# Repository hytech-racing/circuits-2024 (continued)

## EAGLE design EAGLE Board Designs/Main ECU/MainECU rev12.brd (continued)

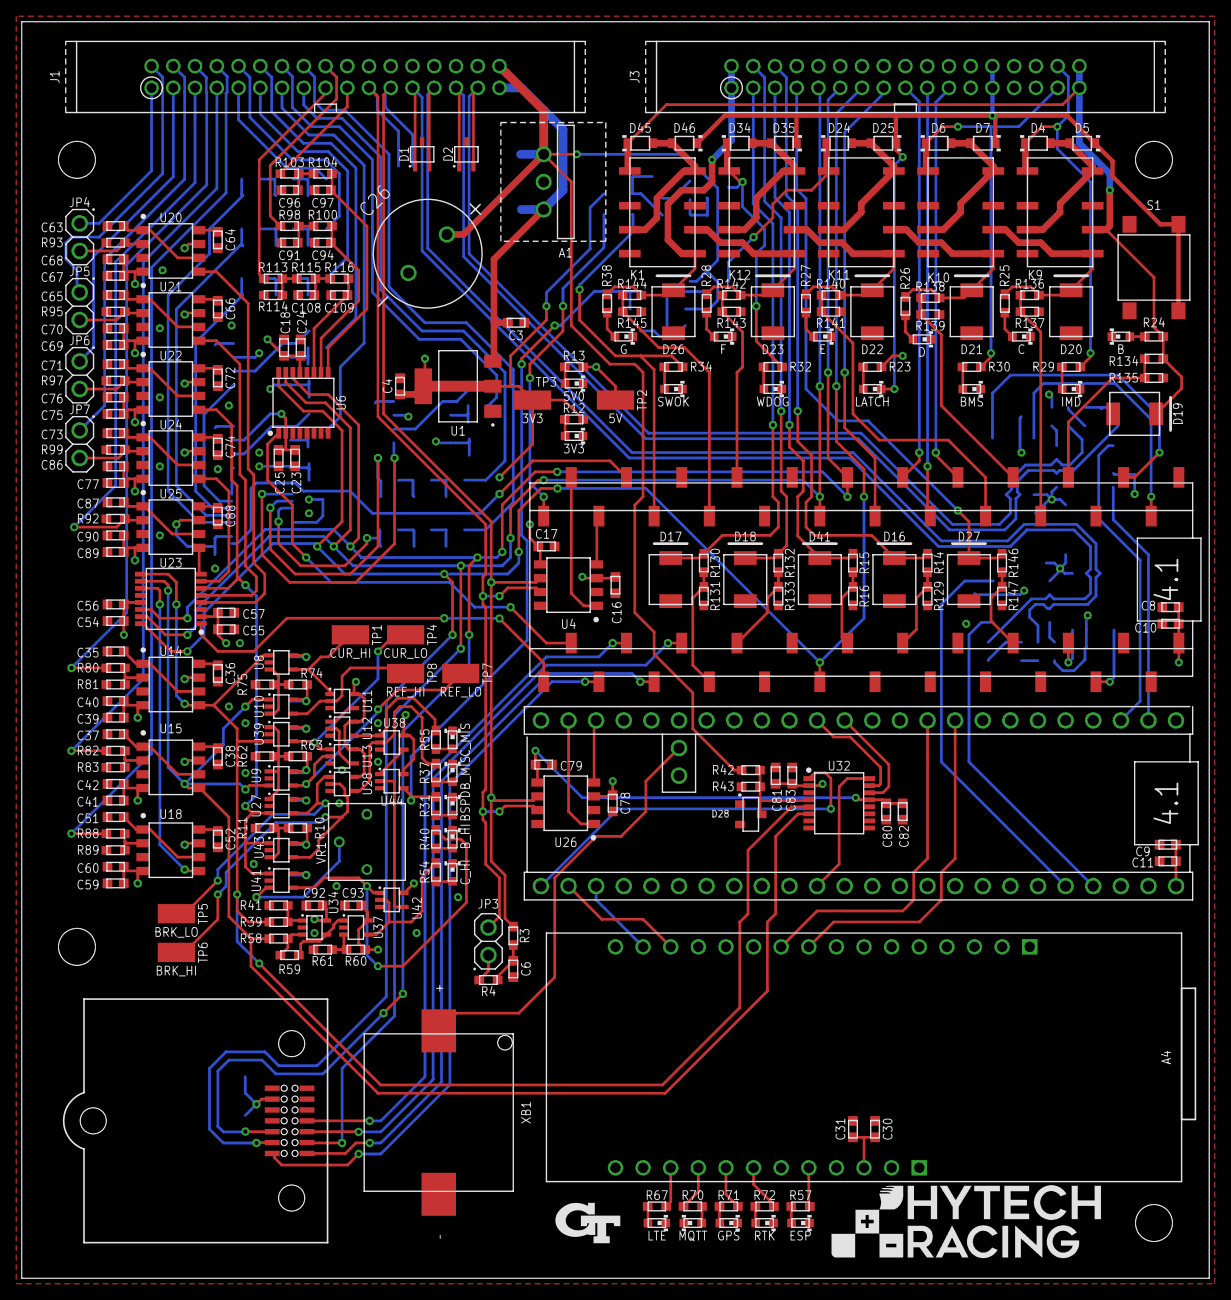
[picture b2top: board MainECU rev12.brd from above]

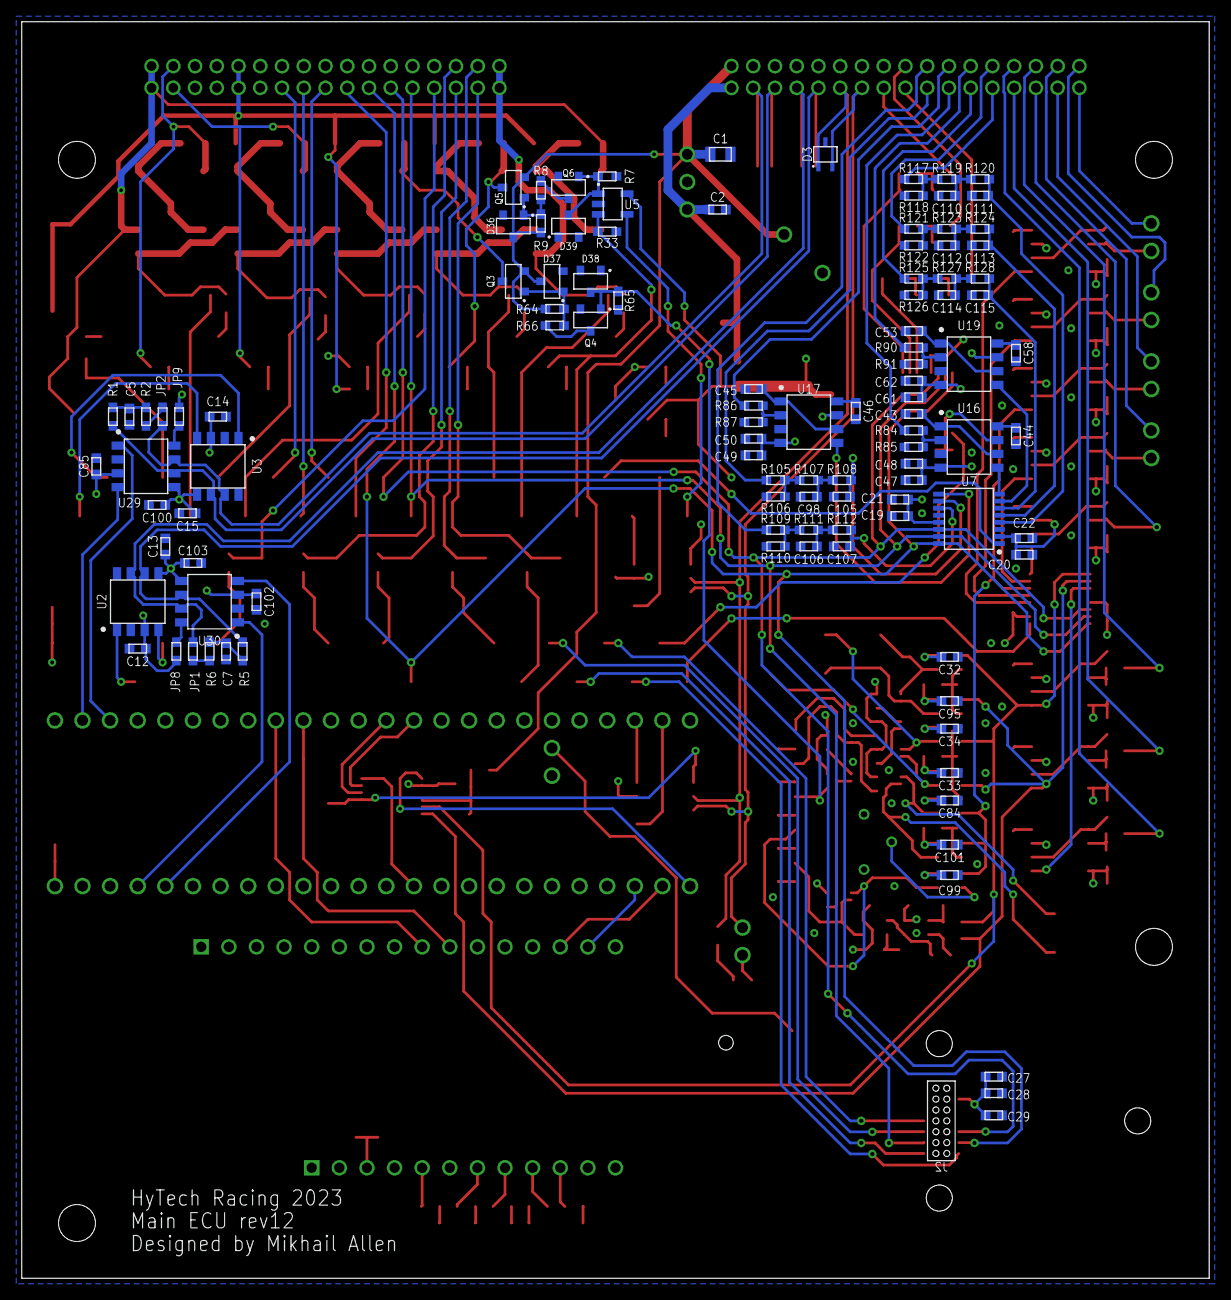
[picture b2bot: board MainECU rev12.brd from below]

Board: 4 copper layers, 109.2 x 115.6 mm, 364 parts (107 on the bottom side), 229 nets.

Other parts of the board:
U$3: LOGO_HYTECH_MEDIUM
U$5: LOGO_GT_SMALL
U$9, U$10, U$11, U$12: MOUNTING_M3

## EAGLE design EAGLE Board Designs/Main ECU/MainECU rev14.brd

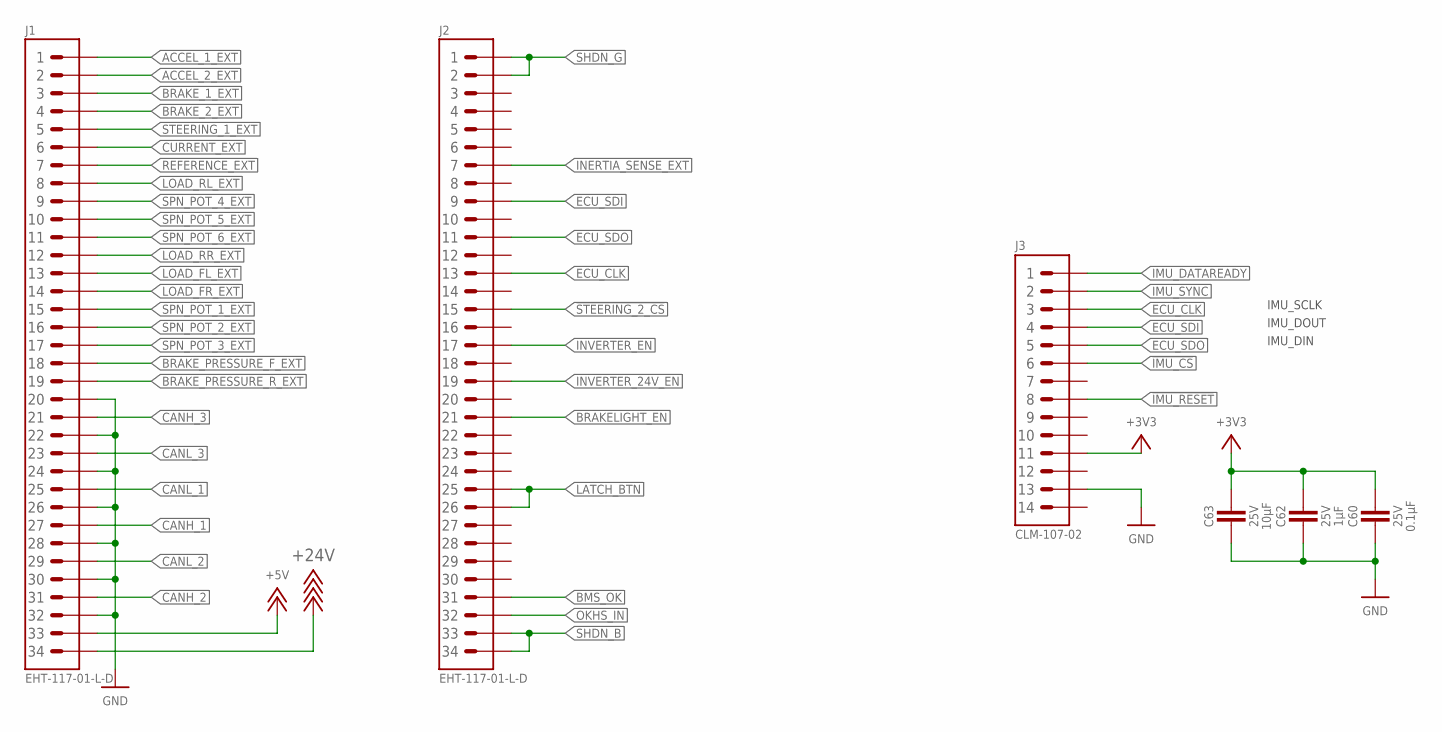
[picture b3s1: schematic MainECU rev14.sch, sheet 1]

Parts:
C60: CAPACITOR_0603_25V_0.1UF; 0603-CAP
C62: CAPACITOR_0603_25V_1UF; 0603-CAP
C63: CAPACITOR_0603_25V_10UF; 0603-CAP
J1, J2: CONNECTOR-34__; EHT-117-01
J3: ADIS16460

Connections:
!IMU_CS: J3.6; also elsewhere on the board
!IMU_RESET: J3.8; also elsewhere on the board
!STEERING_2_CS: J2.15; also elsewhere on the board
+3V3: C60.1, C62.1, C63.1, J3.11; also elsewhere on the board
+5V: J1.33; also elsewhere on the board
+24V: J1.34; also elsewhere on the board
ACCEL_1_EXT: J1.1; also elsewhere on the board
ACCEL_2_EXT: J1.2; also elsewhere on the board
BMS_OK: J2.31; also elsewhere on the board
BRAKELIGHT_EN: J2.21; also elsewhere on the board
BRAKE_1_EXT: J1.3; also elsewhere on the board
BRAKE_2_EXT: J1.4; also elsewhere on the board
BRAKE_PRESSURE_F_EXT: J1.18
BRAKE_PRESSURE_R_EXT: J1.19
CANH_1: J1.27; also elsewhere on the board
CANH_2: J1.31; also elsewhere on the board
CANH_3: J1.21; also elsewhere on the board
CANL_1: J1.25; also elsewhere on the board
CANL_2: J1.29; also elsewhere on the board
CANL_3: J1.23; also elsewhere on the board
CURRENT_EXT: J1.6; also elsewhere on the board
ECU_CLK: J2.13, J3.3; also elsewhere on the board
ECU_SDI: J2.9, J3.4; also elsewhere on the board
ECU_SDO: J2.11, J3.5; also elsewhere on the board
GND: C60.2, C62.2, C63.2, J1.20, J1.22, J1.24, J1.26, J1.28, J1.30, J1.32, J3.13; also elsewhere on the board
IMU_DATAREADY: J3.1; also elsewhere on the board
IMU_SYNC: J3.2; also elsewhere on the board
INERTIA_SENSE_EXT: J2.7; also elsewhere on the board
INVERTER_24V_EN: J2.19; also elsewhere on the board
INVERTER_EN: J2.17; also elsewhere on the board
LATCH_BTN: J2.25, J2.26; also elsewhere on the board
LOAD_FL_EXT: J1.13; also elsewhere on the board
LOAD_FR_EXT: J1.14; also elsewhere on the board
LOAD_RL_EXT: J1.8; also elsewhere on the board
LOAD_RR_EXT: J1.12; also elsewhere on the board
OKHS_IN: J2.32; also elsewhere on the board
REFERENCE_EXT: J1.7; also elsewhere on the board
SHDN_B: J2.33, J2.34; also elsewhere on the board
SHDN_G: J2.1, J2.2; also elsewhere on the board
SPN_POT_1_EXT: J1.15; also elsewhere on the board
SPN_POT_2_EXT: J1.16; also elsewhere on the board
SPN_POT_3_EXT: J1.17; also elsewhere on the board
SPN_POT_4_EXT: J1.9; also elsewhere on the board
SPN_POT_5_EXT: J1.10
SPN_POT_6_EXT: J1.11
STEERING_1_EXT: J1.5; also elsewhere on the board

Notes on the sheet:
IMU_DOUT
IMU_SCLK
IMU_DIN

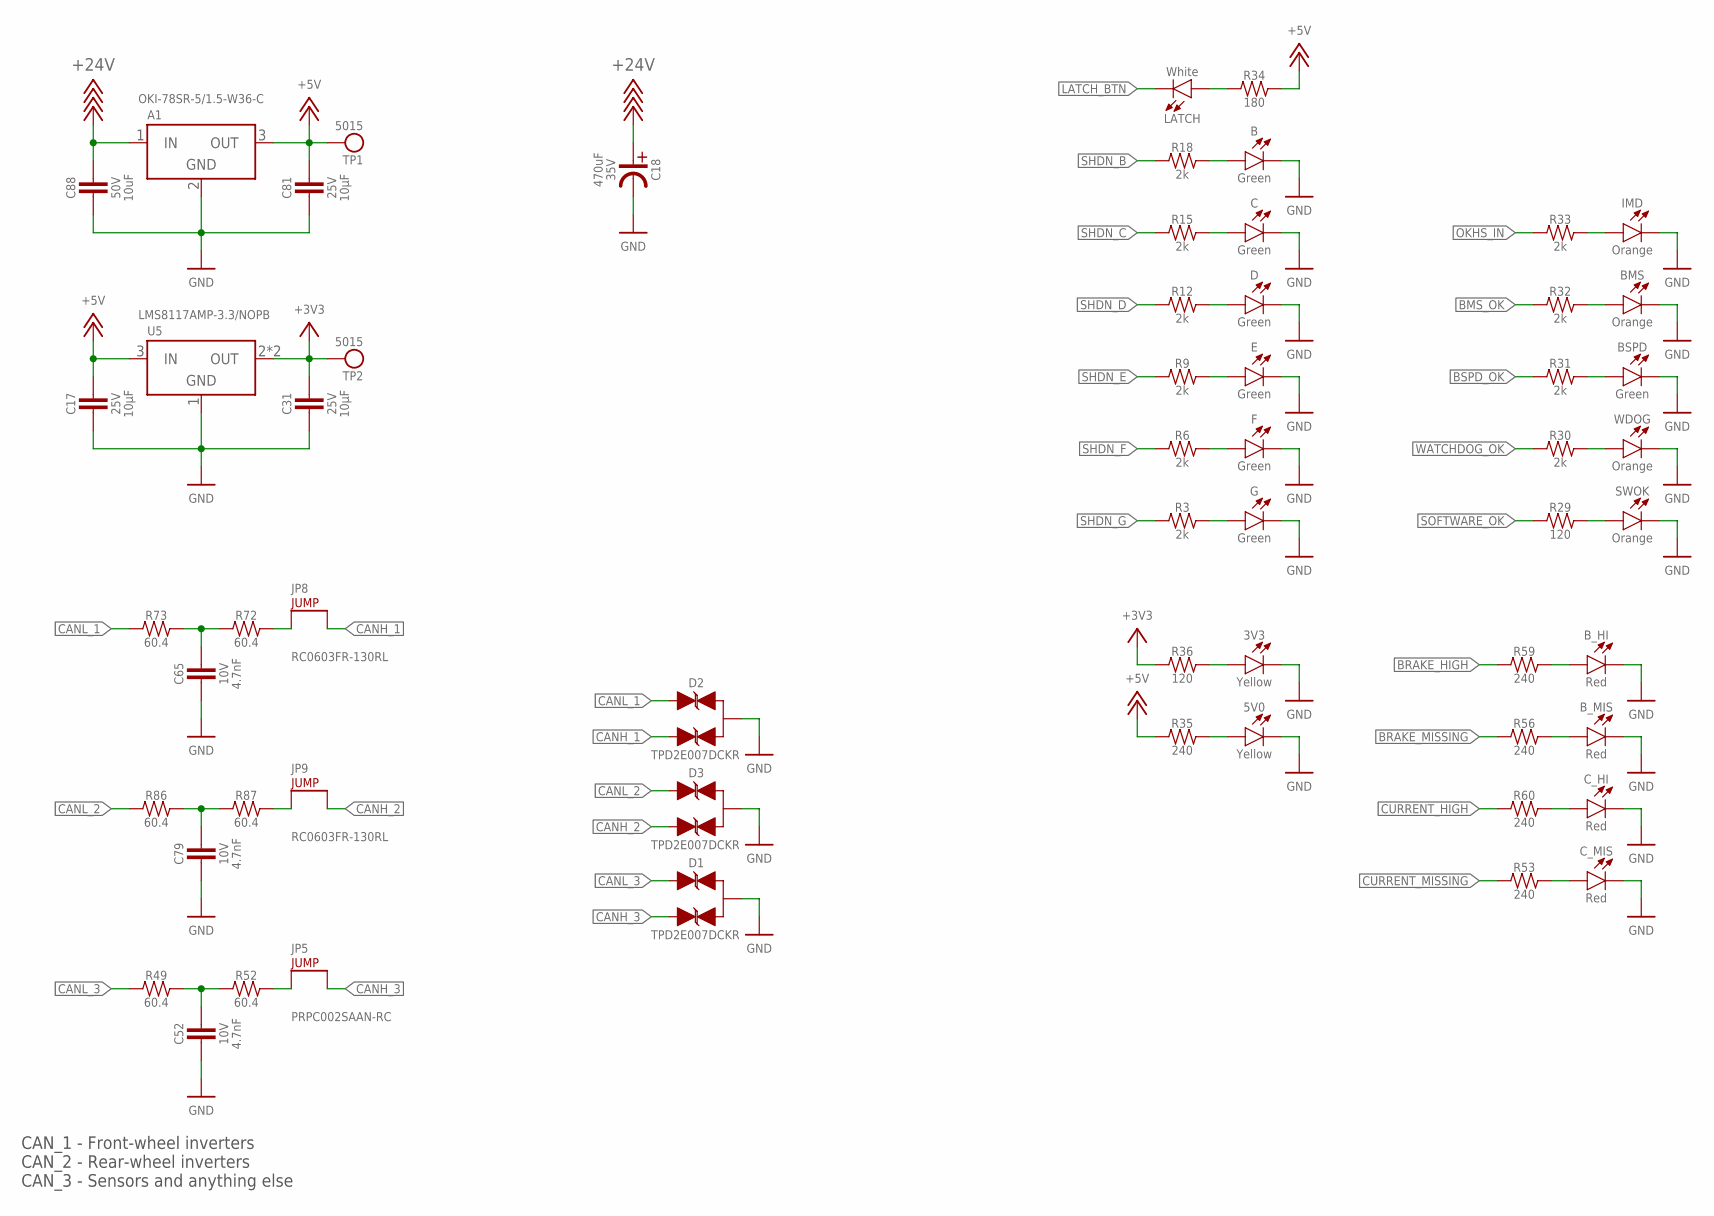
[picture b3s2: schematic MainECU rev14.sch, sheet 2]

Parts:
3V3, 5V0: LED_0603_YELLOW; 0603-LED
A1: VOLTAGE_REGULATOR_MODULE_OKI-78SR_5V; OKI-78SR
B: LED_0603_GREEN; 0603-LED
BMS: LED_0603_ORANGE; 0603-LED
BSPD: LED_0603_GREEN; 0603-LED
B_HI: LED_0603_RED; 0603-LED
B_MIS: LED_0603_RED; 0603-LED
C: LED_0603_GREEN; 0603-LED
C17, C31, C81: CAPACITOR_0603_25V_10UF; 0603-CAP
C18: CAPACITOR_ELECTROLYTIC_EEH_AZS_470UF; EEH-AZS
C52, C65, C79: CAPACITOR_0603_10V_4.7NF; 0603-CAP
C88: CAPACITOR_0805_50V_10UF; 0805-CAP
C_HI: LED_0603_RED; 0603-LED
C_MIS: LED_0603_RED; 0603-LED
D: LED_0603_GREEN; 0603-LED
D1, D2, D3: TVS_BIDIRECTIONAL_DUAL; SC-70-3
E: LED_0603_GREEN; 0603-LED
F: LED_0603_GREEN; 0603-LED
G: LED_0603_GREEN; 0603-LED
IMD: LED_0603_ORANGE; 0603-LED
JP5: JUMPER__1X02; 1X02
JP8, JP9: JUMPER_0603_; 0603-RES
LATCH: LED_0603_WHITE; 0603-LED
R3, R6, R9, R12, R15, R18, R30, R31, R32, R33: RESISTOR_0603_2K; 0603-RES
R29, R36: RESISTOR_0603_120; 0603-RES
R34: RESISTOR_0603_180; 0603-RES
R35, R53, R56, R59, R60: RESISTOR_0603_240; 0603-RES
R49, R52, R72, R73, R86, R87: RESISTOR_0603_60.4; 0603-RES
SWOK: LED_0603_ORANGE; 0603-LED
TP1, TP2: TEST_POINT; 5015
U5: VOLTAGE_REGULATOR_SOT-223_3.3V; SOT-223
WDOG: LED_0603_ORANGE; 0603-LED

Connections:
+3V3: C31.1, R36.1, TP2.1, U5.2 (OUT), U5.4 (OUT); also elsewhere on the board
+5V: A1.3 (OUT), C17.1, C81.1, R34.2, R35.1, TP1.1, U5.3 (IN); also elsewhere on the board
+24V: A1.1 (IN), C18.PLUS, C88.1; also elsewhere on the board
BMS_OK: R32.1; also elsewhere on the board
BRAKE_HIGH: R59.1; also elsewhere on the board
BRAKE_MISSING: R56.1; also elsewhere on the board
BSPD_OK: R31.1; also elsewhere on the board
CANH_1: D2.2 (C2), JP8.2; also elsewhere on the board
CANH_2: D3.2 (C2), JP9.2; also elsewhere on the board
CANH_3: D1.2 (C2), JP5.2; also elsewhere on the board
CANL_1: D2.1 (C1), R73.1; also elsewhere on the board
CANL_2: D3.1 (C1), R86.1; also elsewhere on the board
CANL_3: D1.1 (C1), R49.1; also elsewhere on the board
CURRENT_HIGH: R60.1; also elsewhere on the board
CURRENT_MISSING: R53.1; also elsewhere on the board
GND: 3V3.1 (C), 5V0.1 (C), A1.2 (GND), B.1 (C), BMS.1 (C), BSPD.1 (C), B_HI.1 (C), B_MIS.1 (C), C.1 (C), C17.2, C18.MINUS, C31.2, C52.2, C65.2, C79.2, C81.2, C88.2, C_HI.1 (C), C_MIS.1 (C), D.1 (C), D1.3 (A), D2.3 (A), D3.3 (A), E.1 (C), F.1 (C), G.1 (C), IMD.1 (C), SWOK.1 (C), U5.1 (GND), WDOG.1 (C); also elsewhere on the board
LATCH_BTN: LATCH.1 (C); also elsewhere on the board
unnamed: JP8.1, R72.2
unnamed: JP9.1, R87.2
unnamed: JP5.1, R52.2
unnamed: C79.1, R86.2, R87.1
unnamed: C52.1, R49.2, R52.1
unnamed: C65.1, R72.1, R73.2
unnamed: G.2 (A), R3.2
unnamed: LATCH.2 (A), R34.1
unnamed: B.2 (A), R18.2
unnamed: C.2 (A), R15.2
unnamed: D.2 (A), R12.2
unnamed: E.2 (A), R9.2
unnamed: F.2 (A), R6.2
unnamed: B_MIS.2 (A), R56.2
unnamed: C_HI.2 (A), R60.2
unnamed: C_MIS.2 (A), R53.2
unnamed: IMD.2 (A), R33.2
unnamed: BMS.2 (A), R32.2
unnamed: BSPD.2 (A), R31.2
unnamed: R30.2, WDOG.2 (A)
unnamed: 3V3.2 (A), R36.2
unnamed: R29.2, SWOK.2 (A)
unnamed: 5V0.2 (A), R35.2
unnamed: B_HI.2 (A), R59.2
OKHS_IN: R33.1; also elsewhere on the board
SHDN_B: R18.1; also elsewhere on the board
SHDN_C: R15.1; also elsewhere on the board
SHDN_D: R12.1; also elsewhere on the board
SHDN_E: R9.1; also elsewhere on the board
SHDN_F: R6.1; also elsewhere on the board
SHDN_G: R3.1; also elsewhere on the board
SOFTWARE_OK: R29.1; also elsewhere on the board
WATCHDOG_OK: R30.1; also elsewhere on the board

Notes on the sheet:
CAN_1 - Front-wheel inverters CAN_2 - Rear-wheel inverters CAN_3 - Sensors and anything else

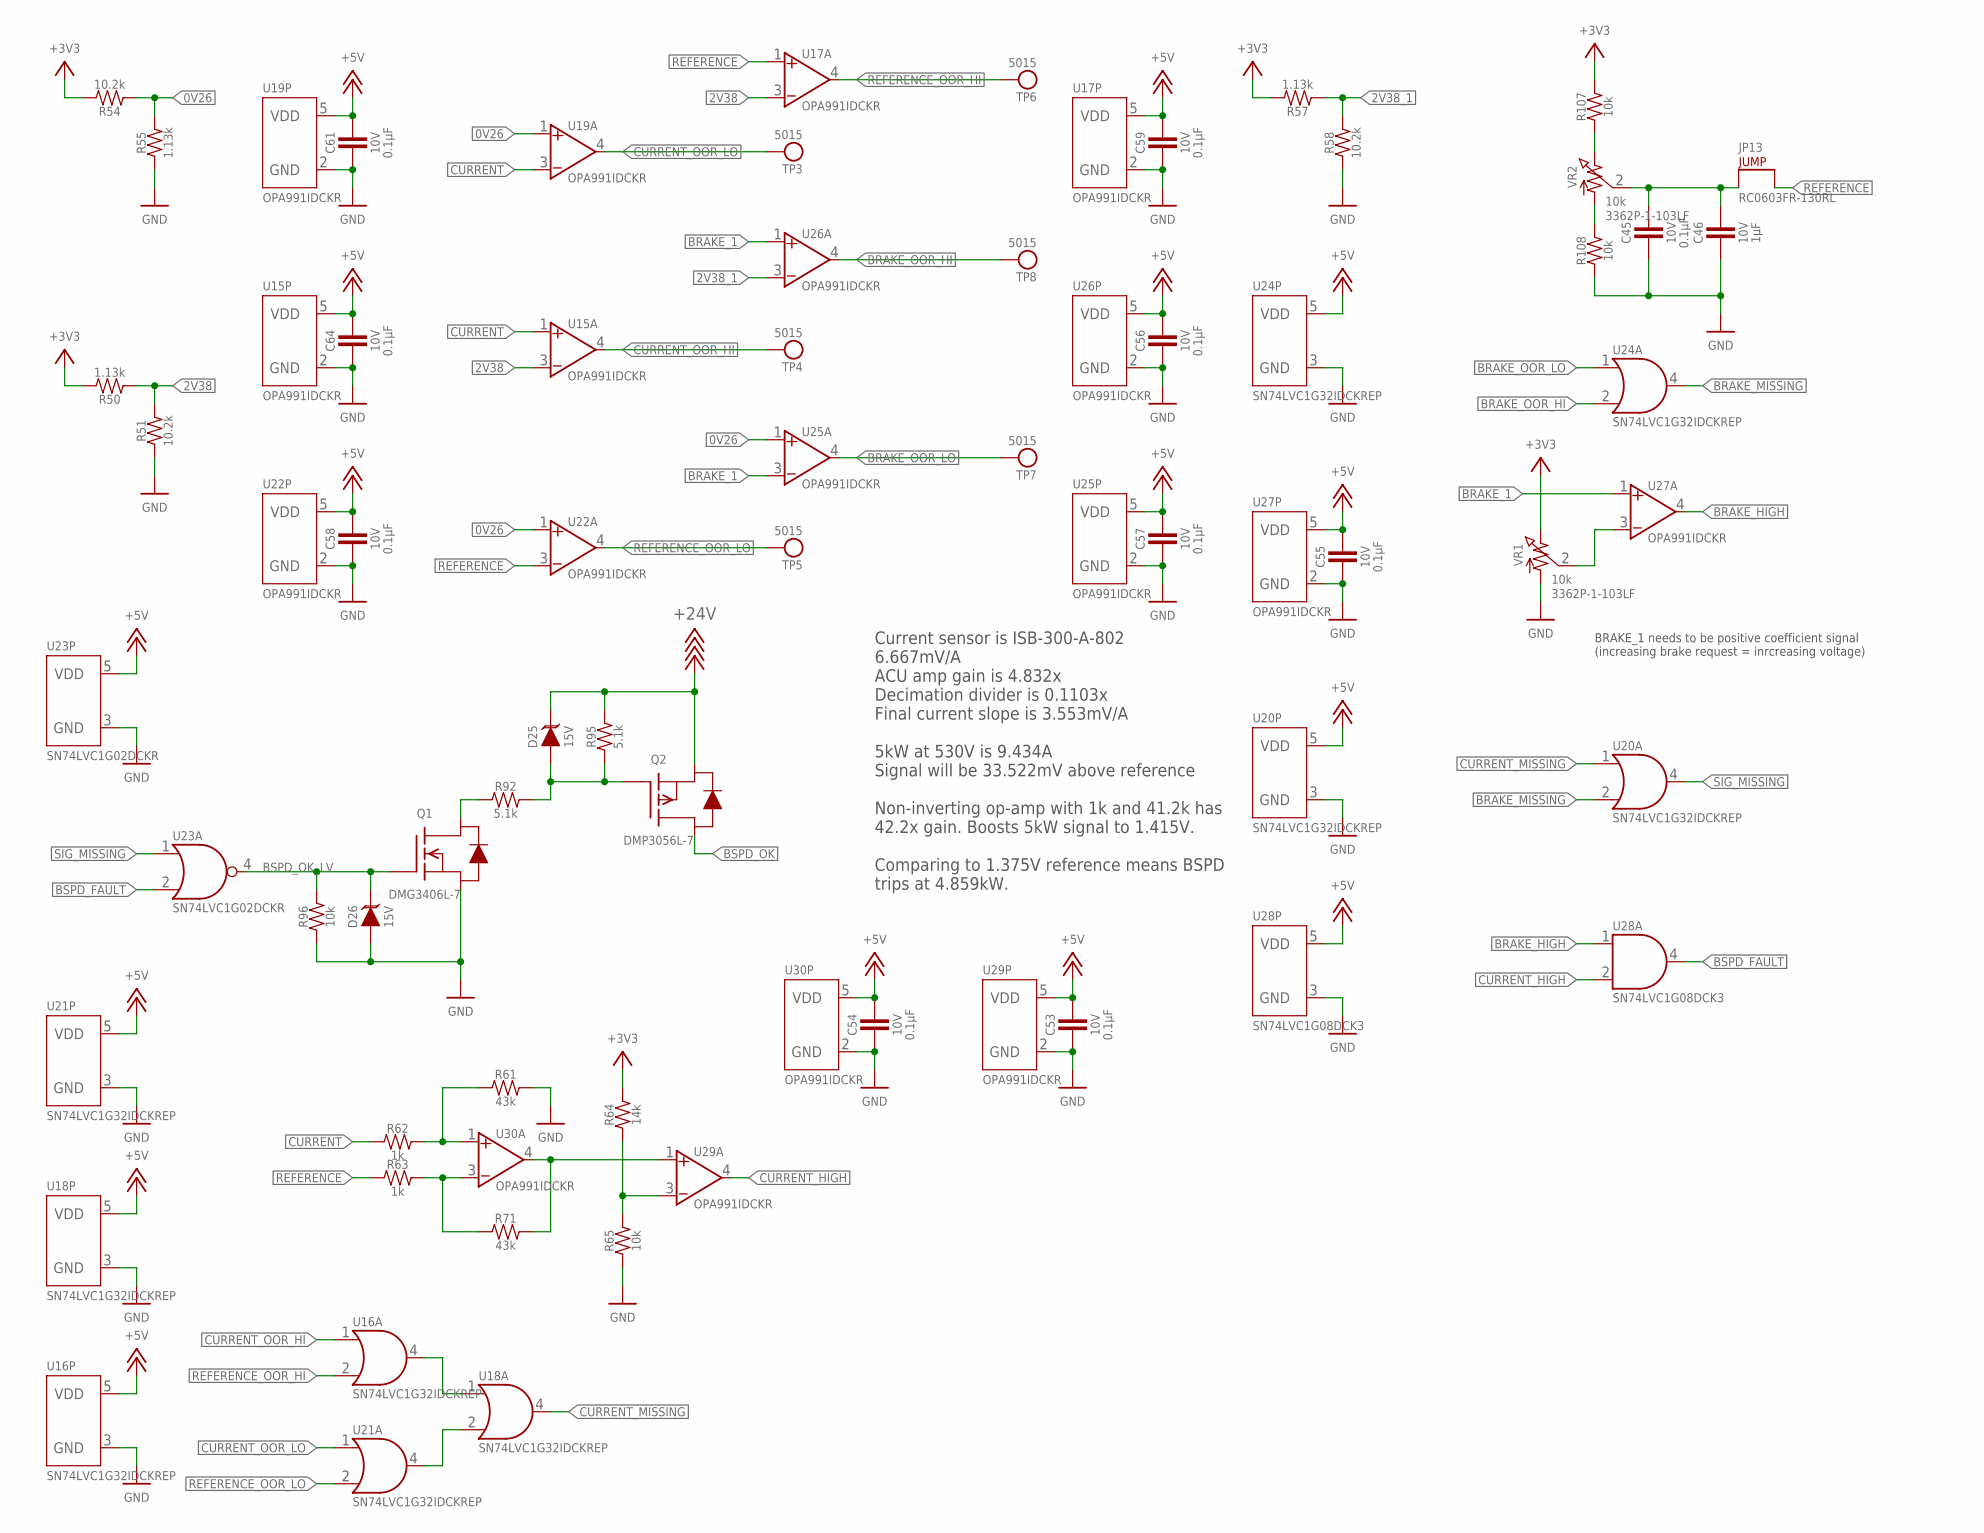
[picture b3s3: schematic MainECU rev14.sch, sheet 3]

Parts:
C45, C53, C54, C55, C56, C57, C58, C59, C61, C64: CAPACITOR_0603_10V_0.1UF; 0603-CAP
C46: CAPACITOR_0603_10V_1UF; 0603-CAP
D25, D26: TVS__15V; SOT-23
JP13: DNP; 0603-RES
Q1: TRANSISTOR_N_MOS__DMG3406L-7; SOT-23
Q2: TRANSISTOR_P_MOS_SOT-23_DMP3056L-7; SOT-23
R50, R55, R57: RESISTOR_0603_1.13K; 0603-RES
R51, R54, R58: RESISTOR_0603_10.2K; 0603-RES
R61, R71: RESISTOR_0603_43K; 0603-RES
R62, R63: RESISTOR_0603_1K; 0603-RES
R64: RESISTOR_0603_14K; 0603-RES
R65, R96, R107, R108: RESISTOR_0603_10K; 0603-RES
R92, R95: RESISTOR_0603_5.1K; 0603-RES
TP3, TP4, TP5, TP6, TP7, TP8: TEST_POINT; 5015
U15, U17, U19, U22, U25, U26, U27, U29, U30: OPAMP_1_CHANNEL_OPA991; SC-70-5
U16, U18, U20, U21, U24: LOGICGATE_OR; SC-70-5
U23: LOGICGATE_NOR; SC-70-5
U28: LOGICGATE_AND_DCK3; SC-70-5
VR1, VR2: RESISTOR_TRIMPOT_10K_3362P; 3362P

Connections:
0V26: R54.1, R55.2, U19.1 (VIN+), U22.1 (VIN+), U25.1 (VIN+)
2V38: R50.1, R51.2, U15.3 (VIN-), U17.3 (VIN-)
2V38_1: R57.1, R58.2, U26.3 (VIN-)
+3V3: R50.2, R54.2, R57.2, R64.2, R107.2, VR1.3 (2); also elsewhere on the board
+5V: C53.1, C54.1, C55.1, C56.1, C57.1, C58.1, C59.1, C61.1, C64.1, U15.5 (VDD), U16.5 (VDD), U17.5 (VDD), U18.5 (VDD), U19.5 (VDD), U20.5 (VDD), U21.5 (VDD), U22.5 (VDD), U23.5 (VDD), U24.5 (VDD), U25.5 (VDD), U26.5 (VDD), U27.5 (VDD), U28.5 (VDD), U29.5 (VDD), U30.5 (VDD); also elsewhere on the board
+24V: D25.3 (C), Q2.2 (S), R95.2; also elsewhere on the board
BRAKE_1: U25.3 (VIN-), U26.1 (VIN+), U27.1 (VIN+); also elsewhere on the board
BRAKE_HIGH: U27.4 (VOUT), U28.1 (IN1); also elsewhere on the board
BRAKE_MISSING: U20.2 (IN2), U24.4 (OUT); also elsewhere on the board
BRAKE_OOR_HI: TP8.1, U24.2 (IN2), U26.4 (VOUT)
BRAKE_OOR_LO: TP7.1, U24.1 (IN1), U25.4 (VOUT)
BSPD_FAULT: U23.2 (IN2), U28.4 (OUT)
BSPD_OK: Q2.3 (D); also elsewhere on the board
BSPD_OK_LV: D26.3 (C), Q1.1 (G), R96.2, U23.4 (OUT)
CURRENT: R62.1, U15.1 (VIN+), U19.3 (VIN-); also elsewhere on the board
CURRENT_HIGH: U28.2 (IN2), U29.4 (VOUT); also elsewhere on the board
CURRENT_MISSING: U18.4 (OUT), U20.1 (IN1); also elsewhere on the board
CURRENT_OOR_HI: TP4.1, U15.4 (VOUT), U16.1 (IN1)
CURRENT_OOR_LO: TP3.1, U19.4 (VOUT), U21.1 (IN1)
GND: C45.2, C46.2, C53.2, C54.2, C55.2, C56.2, C57.2, C58.2, C59.2, C61.2, C64.2, D26.1 (A), Q1.2 (S), R51.1, R55.1, R58.1, R61.2, R65.1, R96.1, R108.1, U15.2 (GND), U16.3 (GND), U17.2 (GND), U18.3 (GND), U19.2 (GND), U20.3 (GND), U21.3 (GND), U22.2 (GND), U23.3 (GND), U24.3 (GND), U25.2 (GND), U26.2 (GND), U27.2 (GND), U28.3 (GND), U29.2 (GND), U30.2 (GND), VR1.1; also elsewhere on the board
unnamed: R61.1, R62.2, U30.1 (VIN+)
unnamed: R107.1, VR2.3 (2)
unnamed: C45.1, C46.1, JP13.1, VR2.2 (3)
unnamed: R108.2, VR2.1
unnamed: R64.1, R65.2, U29.3 (VIN-)
unnamed: R63.2, R71.1, U30.3 (VIN-)
unnamed: R71.2, U29.1 (VIN+), U30.4 (VOUT)
unnamed: U27.3 (VIN-), VR1.2 (3)
unnamed: D25.1 (A), Q2.1 (G), R92.2, R95.1
unnamed: Q1.3 (D), R92.1
OOR_HI: U16.4 (OUT), U18.1 (IN1)
OOR_LO: U18.2 (IN2), U21.4 (OUT)
REFERENCE: JP13.2, R63.1, U17.1 (VIN+), U22.3 (VIN-); also elsewhere on the board
REFERENCE_OOR_HI: TP6.1, U16.2 (IN2), U17.4 (VOUT)
REFERENCE_OOR_LO: TP5.1, U21.2 (IN2), U22.4 (VOUT)
SIG_MISSING: U20.4 (OUT), U23.1 (IN1)

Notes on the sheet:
Current sensor is ISB-300-A-802 6.667mV/A ACU amp gain is 4.832x Decimation divider is 0.1103x Final current slope is 3.553mV/A 5kW at 530V is 9.434A Signal will be 33.522mV above reference Non-inverting op-amp with 1k and 41.2k has 42.2x gain. Boosts 5kW signal to 1.415V. Comparing to 1.375V refer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
BRAKE_1 needs to be positive coefficient signal (increasing brake request = inrcreasing voltage)

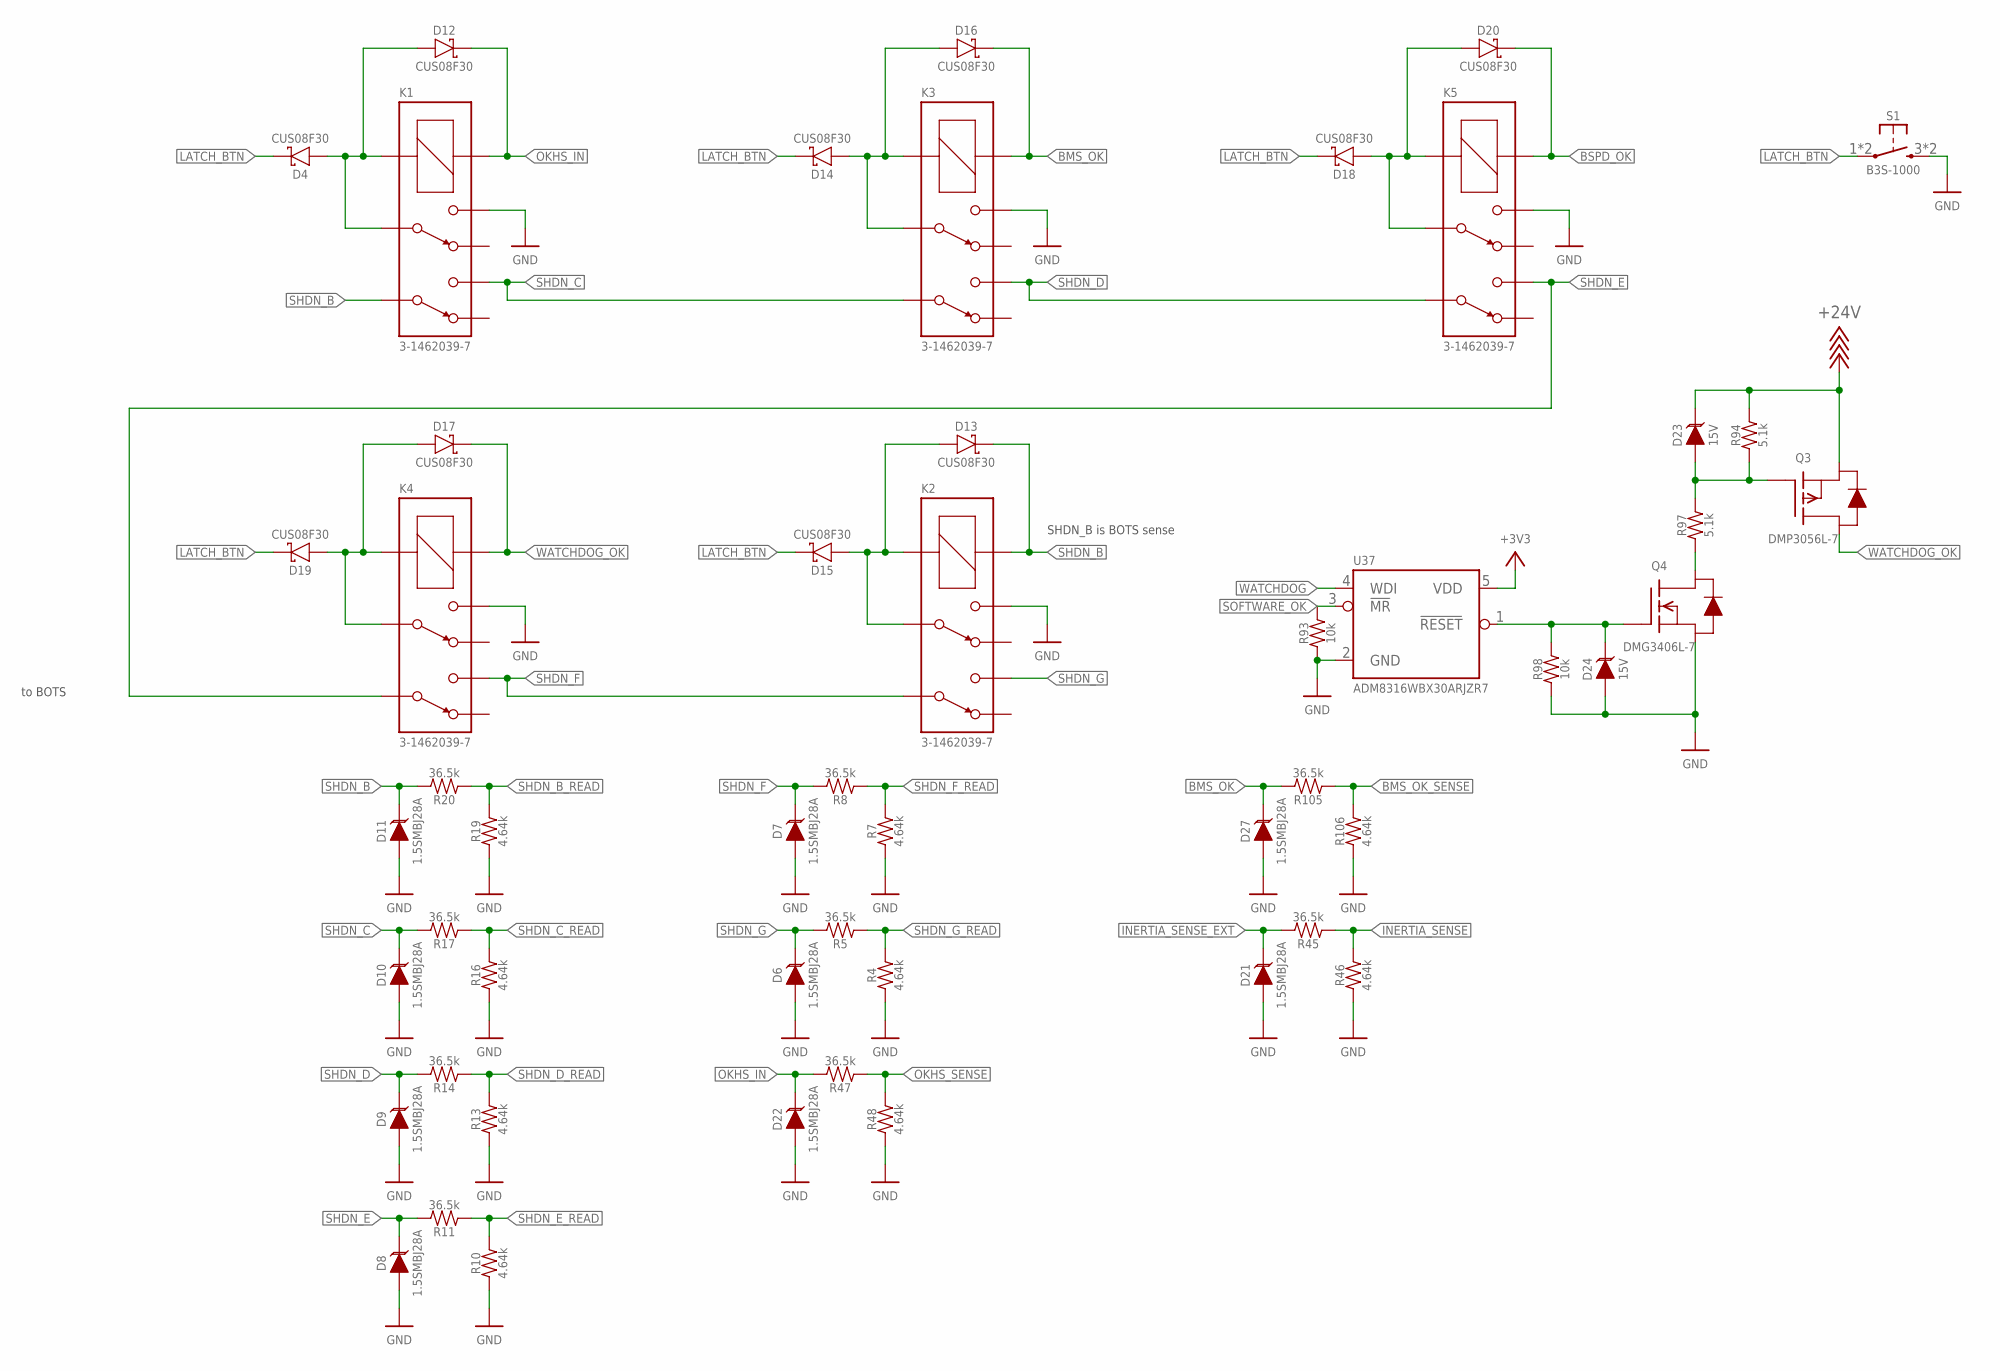
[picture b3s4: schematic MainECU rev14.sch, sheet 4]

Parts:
D4, D12, D13, D14, D15, D16, D17, D18, D19, D20: SCHOTTKY_SOD323_30V; SOD-323
D6, D7, D8, D9, D10, D11, D21, D22, D27: TVS_DO-214AA_28V; DO-214AA
D23, D24: TVS__15V; SOT-23
K1, K2, K3, K4, K5: RELAY_DPDT_07DSMT; IM*G
Q3: TRANSISTOR_P_MOS_SOT-23_DMP3056L-7; SOT-23
Q4: TRANSISTOR_N_MOS__DMG3406L-7; SOT-23
R4, R7, R10, R13, R16, R19, R46, R48, R106: RESISTOR_0603_4.64K; 0603-RES
R5, R8, R11, R14, R17, R20, R45, R47, R105: RESISTOR_0603_36.5K; 0603-RES
R93, R98: RESISTOR_0603_10K; 0603-RES
R94, R97: RESISTOR_0603_5.1K; 0603-RES
S1: BUTTON; B3S-100X
U37: ADM8316WBX30; SOT-23-5

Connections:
+3V3: U37.5 (VDD); also elsewhere on the board
+24V: D23.3 (C), Q3.2 (S), R94.2; also elsewhere on the board
BMS_OK: D16.C, D27.2 (C), K3.1 (COIL+), R105.2; also elsewhere on the board
BMS_OK_SENSE: R105.1, R106.2; also elsewhere on the board
BSPD_OK: D20.C, K5.1 (COIL+); also elsewhere on the board
GND: D6.1 (A), D7.1 (A), D8.1 (A), D9.1 (A), D10.1 (A), D11.1 (A), D21.1 (A), D22.1 (A), D24.1 (A), D27.1 (A), K1.4, K2.4, K3.4, K4.4, K5.4, Q4.2 (S), R4.1, R7.1, R10.1, R13.1, R16.1, R19.1, R46.1, R48.1, R93.1, R98.1, R106.1, S1.3 (S), S1.4 (S), U37.2 (GND); also elsewhere on the board
INERTIA_SENSE: R45.1, R46.2; also elsewhere on the board
INERTIA_SENSE_EXT: D21.2 (C), R45.2; also elsewhere on the board
LATCH_BTN: D4.C, D14.C, D15.C, D18.C, D19.C, S1.1, S1.2; also elsewhere on the board
unnamed: D23.1 (A), Q3.1 (G), R94.1, R97.2
unnamed: Q4.3 (D), R97.1
unnamed: D4.A, D12.A, K1.3, K1.8 (COIL-)
unnamed: D18.A, D20.A, K5.3, K5.8 (COIL-)
unnamed: D14.A, D16.A, K3.3, K3.8 (COIL-)
unnamed: D13.A, D15.A, K2.3, K2.8 (COIL-)
unnamed: D17.A, D19.A, K4.3, K4.8 (COIL-)
OKHS_IN: D12.C, D22.2 (C), K1.1 (COIL+), R47.2; also elsewhere on the board
OKHS_SENSE: R47.1, R48.2; also elsewhere on the board
SHDN_B: D11.2 (C), D13.C, K1.6, K2.1 (COIL+), R20.2; also elsewhere on the board
SHDN_B_READ: R19.2, R20.1; also elsewhere on the board
SHDN_C: D10.2 (C), K1.5, K3.6, R17.2; also elsewhere on the board
SHDN_C_READ: R16.2, R17.1; also elsewhere on the board
SHDN_D: D9.2 (C), K3.5, K5.6, R14.2; also elsewhere on the board
SHDN_D_READ: R13.2, R14.1; also elsewhere on the board
SHDN_E: D8.2 (C), K4.6, K5.5, R11.2; also elsewhere on the board
SHDN_E_READ: R10.2, R11.1; also elsewhere on the board
SHDN_F: D7.2 (C), K2.6, K4.5, R8.2; also elsewhere on the board
SHDN_F_READ: R7.2, R8.1; also elsewhere on the board
SHDN_G: D6.2 (C), K2.5, R5.2; also elsewhere on the board
SHDN_G_READ: R4.2, R5.1; also elsewhere on the board
SOFTWARE_OK: R93.2, U37.3 (!MR!); also elsewhere on the board
WATCHDOG: U37.4 (WDI); also elsewhere on the board
WATCHDOG_OK: D17.C, K4.1 (COIL+), Q3.3 (D); also elsewhere on the board
WATCHDOG_OK_LV: D24.3 (C), Q4.1 (G), R98.2, U37.1 (!RESET!)

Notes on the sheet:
to BOTS
SHDN_B is BOTS sense
